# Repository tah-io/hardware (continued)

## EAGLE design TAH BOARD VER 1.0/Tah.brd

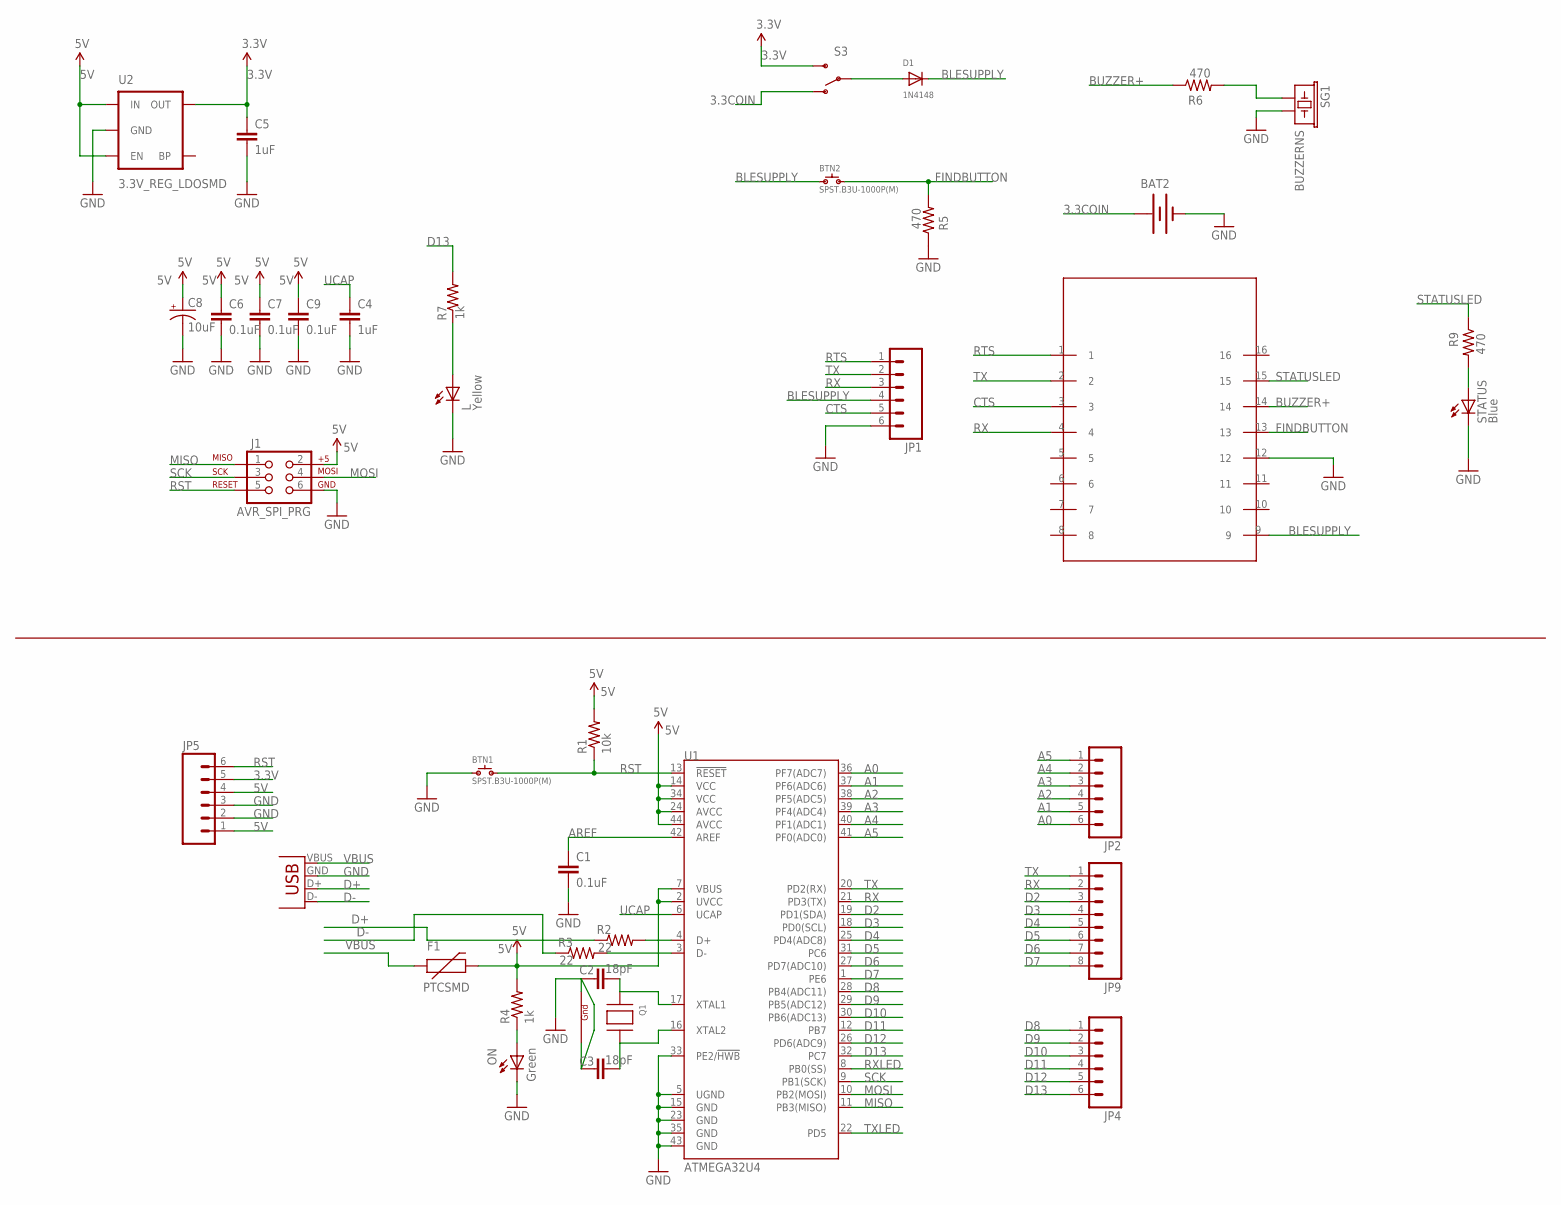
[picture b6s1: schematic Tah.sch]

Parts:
BAT2: BATTERY20SMD; BATTCON_20MM
BLE: HM-11HM11; BC05B-SMD
BTN1, BTN2: SPST.B3U-1000P(M); B3U-1000P(M)
C1, C6, C7, C9: 0.1uF; 1206
C2, C3: 18pF; 1206
C4, C5: 1uF; 1206
C8: 10uF; EIA3216
D1: 1N4148; SMADIODE
F1: PTCSMD; PTC-1206
J1: AVR_SPI_PRG; 2X3
JP1, JP2, JP4, JP5: M06SIP; 1X06
JP7: USB-A-H
JP9: M081X08; 1X08
L: Yellow; 1206
ON: Green; 1206
Q1: XTAL-4-3225; NX3225
R1: 10k; 1206
R2, R3: 22; 1206
R4, R7: 1k; 1206
R5, R6, R9: 470; 1206
S3: SWITCH-SPDT-SMD-A; SWITCH-SPST-SMD-A
SG1: BUZZERNS; BUZZER-12MM-NS
STATUS: Blue; 1206
U1: ATMEGA32U4; SPARKFUN-DIGITALIC_TQFP44
U2: 3.3V_REG_LDOSMD; SOT23-5

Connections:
3.3COIN: BAT2.1 (+), S3.1 (O)
3.3V: C5.1, JP5.5, S3.3 (S), U2.5 (OUT)
5V: C6.1, C7.1, C8.A (+), C9.1, F1.2, J1.2, JP5.1, JP5.4, R1.2, R4.2, U1.2 (UVCC), U1.7 (VBUS), U1.14 (VCC), U1.24 (AVCC), U1.34 (VCC), U1.44 (AVCC), U2.1 (IN), U2.3 (EN)
A0: JP2.6, U1.36 (PF7(ADC7))
A1: JP2.5, U1.37 (PF6(ADC6))
A2: JP2.4, U1.38 (PF5(ADC5))
A3: JP2.3, U1.39 (PF4(ADC4))
A4: JP2.2, U1.40 (PF1(ADC1))
A5: JP2.1, U1.41 (PF0(ADC0))
AREF: C1.1, U1.42 (AREF)
BLESUPPLY: BLE.9, BTN2.1, D1.C, JP1.4
BUZZER+: BLE.14, R6.1
CTS: BLE.3, JP1.5
D2: JP9.3, U1.19 (PD1(SDA))
D3: JP9.4, U1.18 (PD0(SCL))
D4: JP9.5, U1.25 (PD4(ADC8))
D5: JP9.6, U1.31 (PC6)
D6: JP9.7, U1.27 (PD7(ADC10))
D7: JP9.8, U1.1 (PE6)
D8: JP4.1, U1.28 (PB4(ADC11))
D9: JP4.2, U1.29 (PB5(ADC12))
D10: JP4.3, U1.30 (PB6(ADC13))
D11: JP4.4, U1.12 (PB7)
D12: JP4.5, U1.26 (PD6(ADC9))
D13: JP4.6, R7.2, U1.32 (PC7)
D+: JP7.D+ (D-), R2.1
D-: JP7.D- (D+), R3.1
FINDBUTTON: BLE.13, BTN2.2, R5.2
GND: BAT2.2 (-), BLE.12, BTN1.1, C1.2, C2.1, C3.1, C4.2, C5.2, C6.2, C7.2, C8.C (-), C9.2, J1.6, JP1.6, JP5.2, JP5.3, JP7.GND (VBUS), L.C, ON.C, Q1.2 (G2), Q1.4 (G1), R5.1, SG1.- (2), STATUS.C, U1.5 (UGND), U1.15 (GND), U1.23 (GND), U1.33 (PE2/!HWB), U1.35 (GND), U1.43 (GND), U2.2 (GND)
MISO: J1.1, U1.11 (PB3(MISO))
MOSI: J1.4, U1.10 (PB2(MOSI))
unnamed: L.A, R7.1
unnamed: C2.2, Q1.1 (X1), U1.17 (XTAL1)
unnamed: C3.2, Q1.3 (X2), U1.16 (XTAL2)
unnamed: R6.2, SG1.+ (1)
unnamed: R2.2, U1.4 (D+)
unnamed: R3.2, U1.3 (D-)
unnamed: ON.A, R4.1
unnamed: R9.2, STATUS.A
unnamed: D1.A, S3.2
RST: BTN1.2, J1.5, JP5.6, R1.1, U1.13 (!RESET)
RTS: BLE.1, JP1.1
RX: BLE.4, JP1.3, JP9.2, U1.21 (PD3(TX))
RXLED: U1.8 (PB0(SS))
SCK: J1.3, U1.9 (PB1(SCK))
STATUSLED: BLE.15, R9.1
TX: BLE.2, JP1.2, JP9.1, U1.20 (PD2(RX))
TXLED: U1.22 (PD5)
UCAP: C4.1, U1.6 (UCAP)
VBUS: F1.1, JP7.VBUS (GND)

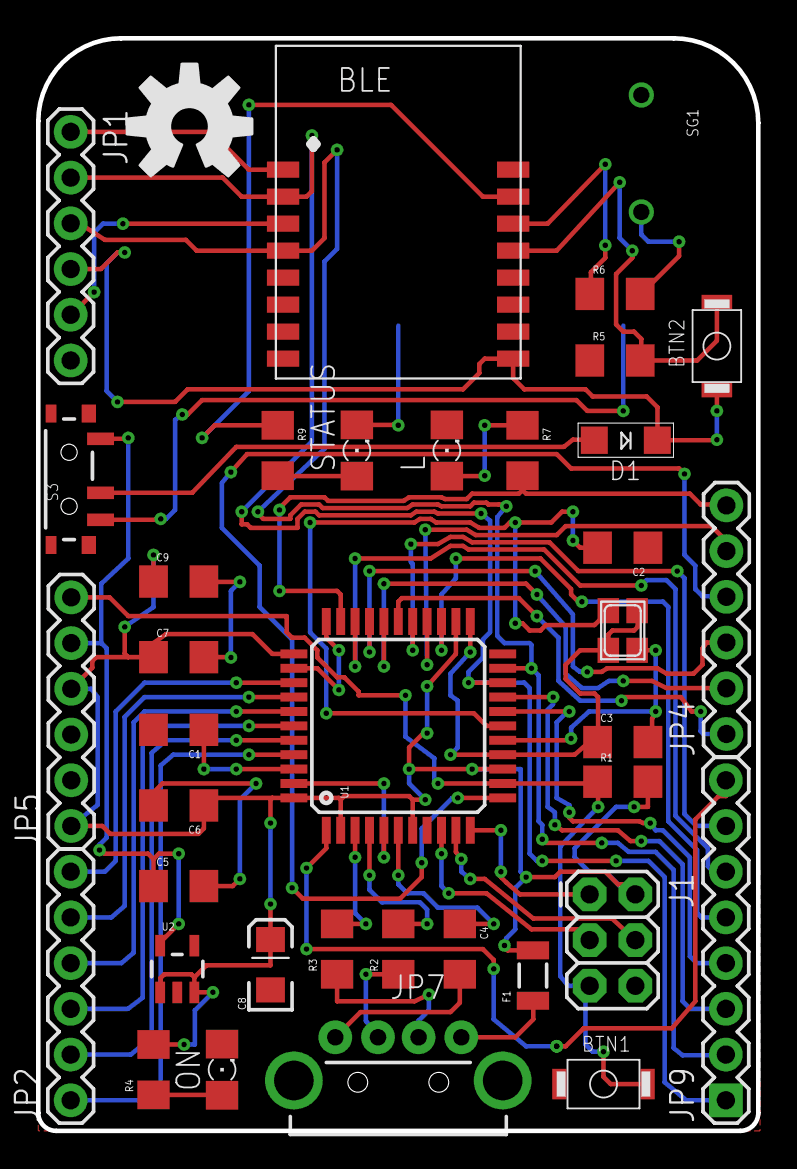
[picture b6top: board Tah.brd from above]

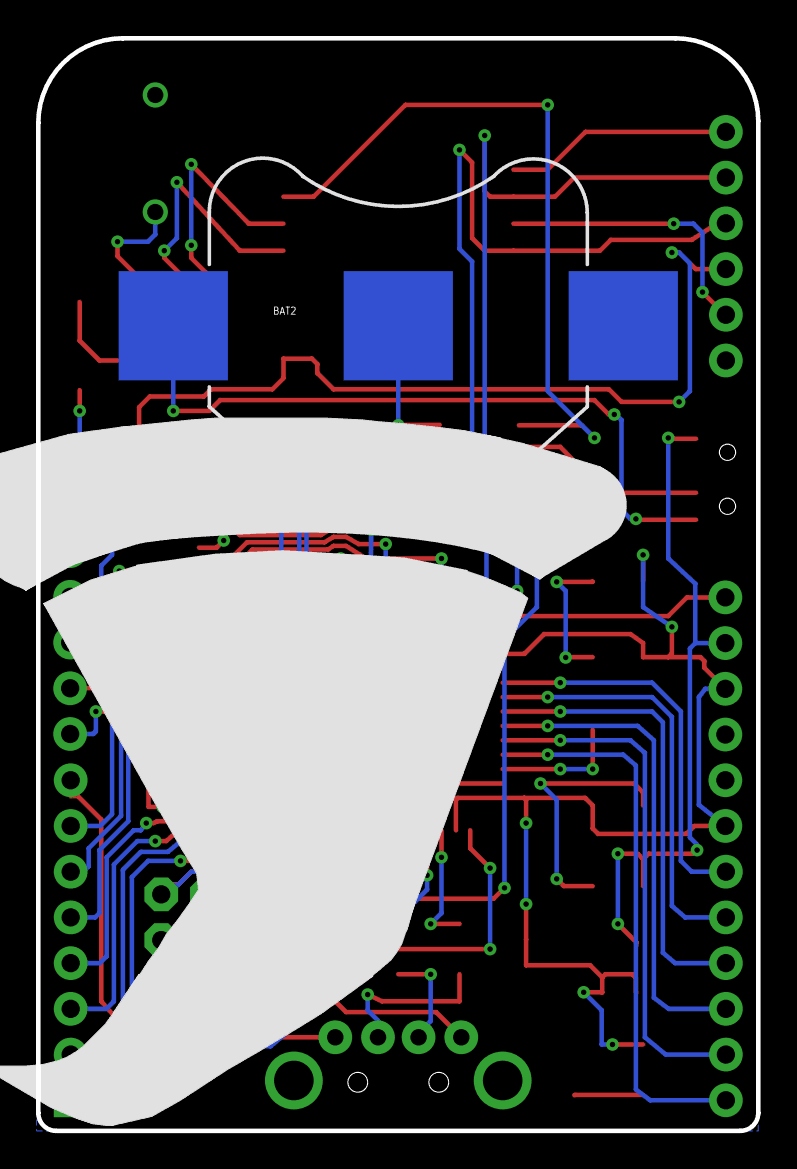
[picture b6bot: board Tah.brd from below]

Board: 2 copper layers, 40.0 x 60.7 mm, 40 parts (2 on the bottom side), 48 nets.

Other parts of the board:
U$1: TAHLOGO
U$3: OSHW-LOGO-L

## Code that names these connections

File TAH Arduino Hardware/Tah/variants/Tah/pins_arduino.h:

#ifndef pins_arduino_h
#define pins_arduino_h

#include <avr/pgmspace.h>

#define TX_RX_LED_INIT	DDRD |= (1<<5), DDRB |= (1<<0)
#define TXLED0			PORTD |= (1<<5)
#define TXLED1			PORTD &= ~(1<<5)
#define RXLED0			PORTB |= (1<<0)
#define RXLED1			PORTB &= ~(1<<0)

static const uint8_t SDA = 2;
static const uint8_t SCL = 3;

// Map SPI port to 'new' pins D14..D17
static const uint8_t SS   = 17;
static const uint8_t MOSI = 16;
static const uint8_t MISO = 14;
static const uint8_t SCK  = 15;

// Mapping of analog pins as digital I/O
// A6-A11 share with digital pins
static const uint8_t A0 = 18;
static const uint8_t A1 = 19;
static const uint8_t A2 = 20;
static const uint8_t A3 = 21;
static const uint8_t A4 = 22;
static const uint8_t A5 = 23;
static const uint8_t A6 = 24;	// D4
static const uint8_t A7 = 25;	// D6
static const uint8_t A8 = 26;	// D8
static const uint8_t A9 = 27;	// D9
static const uint8_t A10 = 28;	// D10
static const uint8_t A11 = 29;	// D12

#define digitalPinToPCICR(p)    ((((p) >= 8 && (p) <= 11) || ((p) >= 14 && (p) <= 17) || ((p) >= A8 && (p) <= A10)) ? (&PCICR) : ((uint8_t *)0))
#define digitalPinToPCICRbit(p) 0
#define digitalPinToPCMSK(p)    ((((p) >= 8 && (p) <= 11) || ((p) >= 14 && (p) <= 17) || ((p) >= A8 && (p) <= A10)) ? (&PCMSK0) : ((uint8_t *)0))
#define digitalPinToPCMSKbit(p) ( ((p) >= 8 && (p) <= 11) ? (p) - 4 : ((p) == 14 ? 3 : ((p) == 15 ? 1 : ((p) == 16 ? 2 : ((p) == 17 ? 0 : (p - A8 + 4))))))

//	__AVR_ATmega32U4__ has an unusual mapping of pins to channels
extern const uint8_t PROGMEM analog_pin_to_channel_PGM[];
#define analogPinToChannel(P)  ( pgm_read_byte( analog_pin_to_channel_PGM + (P) ) )

#ifdef ARDUINO_MAIN

// On the Arduino board, digital pins are also used
// for the analog output (software PWM).  Analog input
// pins are a separate set.

// ATMEL ATMEGA32U4 / Tah
//
// D0				PD2					RXD1/INT2
// D1				PD3					TXD1/INT3
// D2				PD1		SDA			SDA/INT1
// D3#				PD0		PWM8/SCL	OC0B/SCL/INT0
// D4		A6		PD4					ADC8
// D5#				PC6		???			OC3A/#OC4A
// D6#		A7		PD7		FastPWM		#OC4D/ADC10
// D7				PE6					INT6/AIN0
//
// D8		A8		PB4					ADC11/PCINT4
// D9#		A9		PB5		PWM16		OC1A/#OC4B/ADC12/PCINT5
// D10#		A10		PB6		PWM16		OC1B/0c4B/ADC13/PCINT6
// D11#				PB7		PWM8/16		0C0A/OC1C/#RTS/PCINT7
// D12		A11		PD6					T1/#OC4D/ADC9
// D13#				PC7		PWM10		CLK0/OC4A
//
// A0		D18		PF7					ADC7
// A1		D19		PF6					ADC6
// A2		D20 	PF5					ADC5
// A3		D21 	PF4					ADC4
// A4		D22		PF1					ADC1
// A5		D23 	PF0					ADC0
//
// New pins D14..D17 to map SPI port to digital pins
//
// MISO		D14		PB3					MISO,PCINT3
// SCK		D15		PB1					SCK,PCINT1
// MOSI		D16		PB2					MOSI,PCINT2
// SS		D17		PB0					RXLED,SS/PCINT0
//
// TXLED			PD5
// RXLED		    PB0
// HWB				PE2					HWB

// these arrays map port names (e.g. port B) to the
// appropriate addresses for various functions (e.g. reading
// and writing)
const uint16_t PROGMEM port_to_mode_PGM[] = {
	NOT_A_PORT,
	NOT_A_PORT,
	(uint16_t) &DDRB,
	(uint16_t) &DDRC,
	(uint16_t) &DDRD,
	(uint16_t) &DDRE,
	(uint16_t) &DDRF,
};

const uint16_t PROGMEM port_to_output_PGM[] = {
	NOT_A_PORT,
	NOT_A_PORT,
	(uint16_t) &PORTB,
	(uint16_t) &PORTC,
	(uint16_t) &PORTD,
	(uint16_t) &PORTE,
	(uint16_t) &PORTF,
};

const uint16_t PROGMEM port_to_input_PGM[] = {
	NOT_A_PORT,
	NOT_A_PORT,
	(uint16_t) &PINB,
	(uint16_t) &PINC,
	(uint16_t) &PIND,
	(uint16_t) &PINE,
	(uint16_t) &PINF,
};

const uint8_t PROGMEM digital_pin_to_port_PGM[30] = {
	PD, // D0 - PD2
	PD,	// D1 - PD3
	PD, // D2 - PD1
	PD,	// D3 - PD0
	PD,	// D4 - PD4
	PC, // D5 - PC6
	PD, // D6 - PD7
	PE, // D7 - PE6
	
	PB, // D8 - PB4
	PB,	// D9 - PB5
	PB, // D10 - PB6
	PB,	// D11 - PB7
	PD, // D12 - PD6
	PC, // D13 - PC7
	
	PB,	// D14 - MISO - PB3
	PB,	// D15 - SCK - PB1
	PB,	// D16 - MOSI - PB2
	PB,	// D17 - SS - PB0
	
	PF,	// D18 - A0 - PF7
	PF, // D19 - A1 - PF6
	PF, // D20 - A2 - PF5
	PF, // D21 - A3 - PF4
	PF, // D22 - A4 - PF1
	PF, // D23 - A5 - PF0
	
	PD, // D24 / D4 - A6 - PD4
	PD, // D25 / D6 - A7 - PD7
	PB, // D26 / D8 - A8 - PB4
	PB, // D27 / D9 - A9 - PB5
	PB, // D28 / D10 - A10 - PB6
	PD, // D29 / D12 - A11 - PD6
};

const uint8_t PROGMEM digital_pin_to_bit_mask_PGM[30] = {
	_BV(2), // D0 - PD2
	_BV(3),	// D1 - PD3
	_BV(1), // D2 - PD1
	_BV(0),	// D3 - PD0
	_BV(4),	// D4 - PD4
	_BV(6), // D5 - PC6
	_BV(7), // D6 - PD7
	_BV(6), // D7 - PE6
	
	_BV(4), // D8 - PB4
	_BV(5),	// D9 - PB5
	_BV(6), // D10 - PB6
	_BV(7),	// D11 - PB7
	_BV(6), // D12 - PD6
	_BV(7), // D13 - PC7
	
	_BV(3),	// D14 - MISO - PB3
	_BV(1),	// D15 - SCK - PB1
	_BV(2),	// D16 - MOSI - PB2
	_BV(0),	// D17 - SS - PB0
	
	_BV(7),	// D18 - A0 - PF7
	_BV(6), // D19 - A1 - PF6
	_BV(5), // D20 - A2 - PF5
	_BV(4), // D21 - A3 - PF4
	_BV(1), // D22 - A4 - PF1
	_BV(0), // D23 - A5 - PF0
	
	_BV(4), // D24 / D4 - A6 - PD4
	_BV(7), // D25 / D6 - A7 - PD7
	_BV(4), // D26 / D8 - A8 - PB4
	_BV(5), // D27 / D9 - A9 - PB5
	_BV(6), // D28 / D10 - A10 - PB6
	_BV(6), // D29 / D12 - A11 - PD6
};

const uint8_t PROGMEM digital_pin_to_timer_PGM[16] = {
	NOT_ON_TIMER,	
	NOT_ON_TIMER,
	NOT_ON_TIMER,
	TIMER0B,		/* 3 */
	NOT_ON_TIMER,
	TIMER3A,		/* 5 */
	TIMER4D,		/* 6 */
	NOT_ON_TIMER,	
	
	NOT_ON_TIMER,	
	TIMER1A,		/* 9 */
	TIMER1B,		/* 10 */
	TIMER0A,		/* 11 */
	
	NOT_ON_TIMER,	
	TIMER4A,		/* 13 */
	
	NOT_ON_TIMER,	
	NOT_ON_TIMER,
};

const uint8_t PROGMEM analog_pin_to_channel_PGM[12] = {
	7,	// A0				PF7					ADC7
	6,	// A1				PF6					ADC6	
	5,	// A2				PF5					ADC5	
	4,	// A3				PF4					ADC4
	1,	// A4				PF1					ADC1	
	0,	// A5				PF0					ADC0	
	8,	// A6		D4		PD4					ADC8
	10,	// A7		D6		PD7					ADC10
	11,	// A8		D8		PB4					ADC11
	12,	// A9		D9		PB5					ADC12
	13,	// A10		D10		PB6					ADC13
	9	// A11		D12		PD6					ADC9
};

#endif /* ARDUINO_MAIN */
#endif /* pins_arduino_h */

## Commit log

2014-06-27 Initial commit
    Includes the fist 3 revisions of the board
2014-07-03 Arduino TAH Hardware and TAH board 4.0 Eagle files updated
2014-07-25 TAH Shields updated
2014-08-19 TAH Shields new version update
2014-09-23 minor bug fix
2014-11-06 Added latest design files
2014-11-17 All shields updated with latest Tah footprint
2014-11-18 Silk Screen related minor changes
2014-11-18 silk screen related changes
2014-11-20 new tah footprint updated
2014-12-27 Updated production ready files for Tah and shields
2015-01-14 Add BOM
2015-02-27 Tah Arduino Hardware files updated
    *new board files with updated hex
    *Tah eagle library for new footprint
    *Added driver files for Mac and Windows for play app based on Leojoy
2015-03-02 minor driver fixes for windows
2015-03-03 windows driver fix
2015-03-23 updated board files
2015-03-27 latest file update
